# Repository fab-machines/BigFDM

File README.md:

<div align="center"><h1 style="font-family: courier;" align="center">BigFDM</h1></div>

<div align="center"></div>
<div align="center"><i>Open Source Large Scale 3D Printer</i></div>

Premises
--
We dream in a future of freedom, where open source hardware and [Fab Labs](https://fablabs.io/) enable people to fully understand how to make things they need, and where decentralized local production is customized to impact the surrounding community. Believing that empowering the user with knowledge about how to make machines, BigFDM wants to give to the world a powerful open source tool, to 3D print any large scale object you may need. And, together with [LaserDuo](http://laserduo.com/), this is one of the first steps in developing other machines sharing the same philosophy.

BigFDM
--
BigFDM is an open source large scale 3D printer. 

Taking advantage of what we have learned in [Fab Academy](https://fabacademy.org/), BigFDM has been developed using standard [Fab Lab equipment](https://docs.google.com/spreadsheets/d/1U-jcBWOJEjBT5A0N84IUubtcHKMEMtndQPLCkZCkVsU/pub?single=true&gid=0&output=html) and [techniques](http://fab.academany.org/2019/schedule.html). BigFDM was in fact built in [Fab Lab UAE](http://fablabuae.ae/) by Daniele Ingrassia with the help of Hashim Al Sakkaf. Reversing the consumer process, where knowledge and building of machines stays inside a black box managed by companies, BigFDM brings the advantages of an open source development:

- full awareness about how the machine works
- reproducible design
- possibility to customize the machine and/or to build new ones
- built as much as possible with local materials
- local self-fixing and self-production of the machine parts
- community can use and improve the design
- cheap alternative to large scale 3D printers
- use BigFDM as tool to produce other open source machines

BigFDM allows the printing of large scale objects, some examples can be orthotics and prosthesis, art installations, furniture, replacement parts, industrial design prototypes, molds for casting of full scale parts. Using  Fused Deposition Modeling (or FDM), it can use standard 2.85mm 3D printer filament, and as well common extruders nozzles.

**BigFDM specifications**:

- **800mm x 800mm x 900mm** printing area
- **dual extruder** with interchangeble nozzle
- **2.85mm** filament
- **0.4 - 1mm** nozzle size
- **NEMA 24/23**  stepper motors
- stages with **HiWin linear guides**
- anodized **aluminium frame**
- **heated bed** with 4 x 750W bed heaters
- **closed housing** of aluminum composite and acrylic
- fabbable **[satshakit](https://github.com/satshakit) and [satstep](https://github.com/satstep)** based electronics
- **integrated tablet** for machine control
- printing from **USB** drive
- BOM cost of about **2600€**
- power requirements 220V, 3000W max

Machine design
--

BigFDM has been designed considering to keep fixed from the beginning few constraints, which then influenced the rest of the subsequent design choices:

- the all machine parts must be inside a boxed main frame
- the machine XY stages design must be independent and consistent by itself
- the Z axis moves the bed up or down

These have been tought in order to bring the following benefits:

- a **compact design** that maximize the printing area while minizing the unused space (just 2mm between the bed supports and the housing!)
-  minimizing the unused space has **lowered the cost** of the frame and the housing parts
-  the main frame serves both as **structural squared reference** for all the machine parts and well as body for the housing
-  the **XY stages can be completely removed** without disassembling any other machine section
-  the **XY stage indipendent design** can be reused to develop other machines
-  the machine printing **area can be scaled up/down** just by changing the length of few machine parts

X and Y stages
--

The X and Y stages integrates all their components inside a squared plane frame of T-Slots profiles. Hiwin 15mm linear guides and 10mm GT2 belts, together with custom CNC milled POM parts have been used. Implementing a sort of **stages interoperability**, the stages frame can be completely detached from the machine, and virtually, plugged into a different machine having similar frame shape (eg a laser cutter). Similar interoperability has also been recursively kept for the Y axis, which can be modified/removed without changing the X axis. 

Z axis
--

The Z axis uses a single NEMA 24 to move 4 lead screws guided by 4 linear rods and bearings. A 4.7m closed loop HTD M3 belt is used to transmit the movement with a 2 to 1 pulley ratio. The lead screws are supported by ball bearing both at the top and the bottom, where also pulleys are attached. The corner structural parts are made with CNC milled 20mm acrylic, while the rods and bearing supports use CNC milled POM. Because of layer by layer downwards needed movements, the bed will never move fast, with the maximum speed used more for manual movements. The main frame is used as support structure for all the Z axis parts.

Bed
--

Made out of a 6mm aluminum plate cut with the CNC, the printing bed is suspended onto a lower frame structure by using 4 x 8mm DIN 912 bolts. The lower bed frame in turn is attached to the Z axis lead screws and linear rods. The lower frame is kept parallel to the upper stages by mechanically aligning it during the assembly, while the printing bed flatness can be finely tuned by screwing/unscrewing the 4 bolts. The design of the printing bed takes into account its **thermal expansion**, leaving a tolerance of expansion that exceeds the calculated one from the aluminum.

Housing
--

The housing has been developed to keep the internal temperature stable, and to allow the bed to quickly warmup. Because the machine parts have been constrained to be inside, the housing is attached directly to the main frame, and no additional parts are needed. The corners are made by 4mm aluminum composite (also called as dibond), while the windows are 6mm acryllic. Both materials have been CNC milled and the design is made in a way to fit two full sheets (about 2400x1250mm) of acrylic and one of aluminum composite. The tablet enclousure is made with the same materials, and allows to quickly remove it from the top.

Electronics
--
The electronics of BigFDM consists of a set of fabbable electronics, derived from the original **[satshakit](https://github.com/satshakit)** board and **[satstep](https://github.com/satstep)** stepper drivers, plus some additional boards. Following the used boards and their role in BigFDM.<br>

**[satshakit-mega](https://github.com/fab-machines/BigFDM/tree/master/electronics/satshakit-mega)**

Based on the [ATMega2560](https://www.microchip.com/wwwproducts/en/ATmega2560), this board provides the necessary microcontroller hardware for the Marlin manage its logic functionalities. Furthermore integrates an USB-to-Serial converter and USB port. Developed as general purpose board, not all the pins will be used. In the future this board will be a custom made solution for BigFDM. Link to the original [repo](https://github.com/satshakit/satshakit-mega).

---------

**[satstep6600](https://github.com/fab-machines/BigFDM/tree/master/electronics/satstep6600)**

Proved to have a robust design by being used in **[LaserDuo](http://laserduo.com/)** for more than a year, the satstep6600 is the stepper driver used to move the NEMA 23/24 used in BigFDM. Based on the Toshiba [TB6600HG](http://www.massmind.org/images/massmind/TB6600HG_datasheet.pdf) it can give up to 4.5A per coil to a single motor, whereas the NEMA 24 used will take a maximum of 4A. Link to the original [repo](https://github.com/satstep/satstep6600).

---------

**[Mosftet Board](https://github.com/fab-machines/BigFDM/tree/master/electronics/mosfet-board)**

Developed as an add-in to the satshakit-mega for BigFDM, the mosfet board integrates 4 mosfets to drive the nozzle heaters and the solid stae relay for the bed heaters, plus two slots for Pololu A4988 or similar stepper drivers. The A4988 are used to drive the two nozzle stepper motors.

---------

**[Sensor Board](https://github.com/fab-machines/BigFDM/tree/master/electronics/sensor-board)**

The sensor board integrates simple design with filtering capacitors and pull-up resistor. To this board the thermistors from the extruder and one of the thermistor of the bed heaters will be connected, together with the analog pins from the satshakit-mega.

---------

**[Endstop Board](https://github.com/fab-machines/BigFDM/tree/master/electronics/endstop-board)**

In a similar way of the Sensor Board, the Endstop Boards has some pull-up resistors and some capacitors to filter the noise coming from the endstops. To this board the endstops and the limits min (x-min, y-min, z-min) from the satshakit-mega will be connected. BigFDM uses normally open endstops. 

---------

Summary of the needed boards:

- 1 x satshakit-mega
- 3 x satstep6600
- 1 x mosfet board
- 1 x endstop board
- 1 x sensor board

To power all this electronics, and to switch on and off the heaters the following additonal parts are needed:

- 15A 24V power supply
- 25A 12V power supply
- 25A 230V solid state relay
- 3 x 24V fans (for the 3 x satstep6600)

Software
--
BigFDM uses **[Marlin firmware](https://github.com/MarlinFirmware/Marlin)** running on the satshakit-mega. The configuration changes have been applied into the configuration.h file, you can find it in the [config](https://github.com/fab-machines/BigFDM/tree/master/config) folder of this repository.

To control the machine and to stream the G-Code, [Repetier-Host](https://www.repetier.com/) has been used.

Build your own BigFDM
--

BigFDM is made by using a mix of fabricated and ready-made parts. The ready-made parts are selected to be as common/standard as possible, to make the sourcing of them easy in many countries. For both the raw materials needed for the fabricated parts, and the ready-made parts, refer to the Bill-of-Material for details: **[BigFDM BOM](https://github.com/fab-machines/BigFDM/raw/master/docs/BigFDM%20BOM.pdf)**

The fabrication of the parts mainly relays on standard [Fab Lab equipment](https://docs.google.com/spreadsheets/d/1U-jcBWOJEjBT5A0N84IUubtcHKMEMtndQPLCkZCkVsU/pub?single=true&gid=0&output=html). It will be therefore possible to make BigFDM in any of Fab Labs worldwide having it. Below a list of the required tools and machines:

- C02 laser cutter:
 - able to cut 8mm acrylic
 - needed for small acrylic parts
- large format wood CNC machine:
 - ShopBot or similar, size 2500x1250mm
 - to machine the aluminum parts (bed, Z axis supports)
 - to machine the aluminum composite for the housing
 - to machine the acrylic for the housing windows
 - to machine the POM parts (motor holders, attachments)
- 3D printer:
 - a small one (20x20x20cm) is sufficient
 - to print the filament/cables holders 
- Desktop format CNC machine:
 - Roland MDX50/MDX20/SRM20 or similar small machine (as well the cheap chinese ones)
 - to produce the required PCBs
- standard set of tools:
 - spanner key set
 - hex key set
 - DIN 875
 - calipers
 - rulers
 - screwdriver set
 - player set (grabber/cutter etc..)
 - clamps
 - rubber hummers

Both fabricated and ready-made parts have been modeled inside the **[BigFDM Fusion 360 model](https://github.com/fab-machines/BigFDM/raw/master/cad/BigFDM.f3d)**. Using Fusion is possible to export/prepare the parts for production in the following ways:

- right click save as STL, on a body that needs to be 3D printed
- use the built-in Fusion CAM processor for the machined parts
- project on a surface, and then right click export as DXF, for laser cutting
 
For more details about the tools and once you have all the fabricated and ready-made parts parts available, refer to the for step-by-step assembly instructions and tips: **[BigFDM Building Manual](https://github.com/fab-machines/BigFDM/wiki/Big-FDM-Building-Manual)** 

Big FDM requires different fabbable PCBs to work. Below the download links for the eagle files that you use to fabricate them:

- **[satshakit-mega schematic](https://raw.githubusercontent.com/fab-machines/BigFDM/master/electronics/satshakit-mega/satshakit-mega.sch)**, **[satshakit-mega board](https://raw.githubusercontent.com/fab-machines/BigFDM/master/electronics/satshakit-mega/satshakit-mega.brd)**
- **[satstep6600 schematic](https://github.com/fab-machines/BigFDM/raw/master/electronics/satstep6600/satstep6600.sch)**, **[satstep6600 board](https://github.com/fab-machines/BigFDM/raw/master/electronics/satstep6600/satstep6600.brd)**
- **[mosfet board schematic](https://github.com/fab-machines/BigFDM/raw/master/electronics/mosfet-board/mosfer-board.sch)**, **[mosfet board](https://github.com/fab-machines/BigFDM/raw/master/electronics/mosfet-board/mosfet-board.brd)**
- **[sensor board schematic](https://github.com/fab-machines/BigFDM/raw/master/electronics/sensor-board/sensor-board.sch)**, **[sensor board](https://github.com/fab-machines/BigFDM/raw/master/electronics/sensor-board/sensor-board.brd)**
- **[endstop board schematic](https://github.com/fab-machines/BigFDM/raw/master/electronics/endstop-board/endstop-board.sch)**, **[endstop board](https://github.com/fab-machines/BigFDM/raw/master/electronics/endstop-board/endstop-board.brd)**

Download here the configuration files (right click save as):

- **[Marlin BigFDM](https://github.com/fab-machines/BigFDM/raw/master/config/Marlin-1.1.x-BIGFDM.zip)** 
- **[Cura profile settings for 1mm nozzle](https://github.com/fab-machines/BigFDM/raw/master/config/Cura_BigFDM.curaprofile)** 
- **[Cura  machine settings](https://github.com/fab-machines/BigFDM/raw/master/config/BigFDM_machine_settings.png)**
- **[Cura extruder settings](https://github.com/fab-machines/BigFDM/raw/master/config/BigFDM_extruder_settings.png)**

Known issues
--

- the extruder used is a dual Geetech MK8, which is good up to 0.5mm nozzle but has difficulties in keeping the temperature with an 1mm nozzle; in the future will be replaced by a custom made extruder supporting nozzles up to 2mm

- because of the difficulties for the extruder to warmup, to save time it is recommended to start heating it manually whenever possible before starting printing 

- the electronics setup requires improvements, especially a custom made board in place of the satshakit-mega and an additonal all-in-one board, replacing the mosfet, sensor and endstop boards

- the Z axis design needs multiple parts for the supporting corners of the lead screws and the linear rods; in the future replaced by an unique block of CNC milled aluminum

- the G-Code streaming from the tablet is sometimes gets corrupted and/or interrupts suddenly; is needed to use an higher quality shielded USB cable, or  to try Octoprint instead of Repetier host as G-Code streamer

Media
--
**BigFDM printing**

**How to Make BigFDM: Tunisia Workshop at [Fab Lab ENIT](https://www.facebook.com/FabLabENIT/)**

**BigFDM pictures**

<br><br><br>

<br><br><br>

<br><br><br>

Author
--

The author of BigFDM is:

- **Daniele Ingrassia, daniele@inmachines.net**
- **[InMachines Ingrassia GmbH](https://www.inmachines.net/)**

**Project Helper:**<br>
- **[Hashim Al Sakkaf](http://archive.fabacademy.org/fabacademy2017/fablabuae/students/154/)**

Donations
--

Our dream is to have impact by making **open source machines digitally available and locally produced anywhere in world**. We plan to open a dedicated Fab Lab to foster open machine building and digital fabrication research. Practically several tasks and many expensens have to be sustained to give this dream the chance to have a future. Such as the renting of a proper space, the making/purchasing of proper equipment, the sustainability of our work and lifes. If you share this mindset and BigFDM is useful to you, please help us to make this dream a reality by donating your support:

Acknowledgements
--

The development of this machine has been funded by:<br>
**[German Federal Ministry of Education and Research](https://www.bmbf.de/en/index.html)**

Funds implemented by:<br>
**[OpenLab Hamburg](http://openlab-hamburg.de/startpage/)**<br>
[Helmut-Schmidt-Universität Universität der Bundeswehr](https://www.hsu-hh.de/en/)<br>
Laboratorium Fertigungstechnik<br>
Holstenhofweg 85<br>
22043 Hamburg<br>

Thanks:<br>
<br>
**[Fablab UAE](http://fablabuae.ae/)**<br />
176 6 D St - Satwa <br />
Dubai - United Arab Emirates<br />
fablabuae@gmail.com

**Paul Anand**

License
-- 
The BigFDM, its hardware design, CAD, BOM, settings and relative files are are released under the following open source license:

- CERN Open Hardware Licence Version 2 Weakly Reciprocal - **[CERN-OHL-W](LICENSE_CERN_OHL_W_V2.txt)**

Note
--

This documentation will be continuously improved as soon there are updates and/or improvements on the machine.

Disclaimer  
--

<div class="align-justify">
This hardware/software is provided "as is", and you use the hardware/software at your own risk. Under no circumstances shall any author be liable for direct, indirect, special, incidental, or consequential damages resulting from the use, misuse, or inability to use this hardware/software, even if the authors have been advised of the possibility of such damages.</div>

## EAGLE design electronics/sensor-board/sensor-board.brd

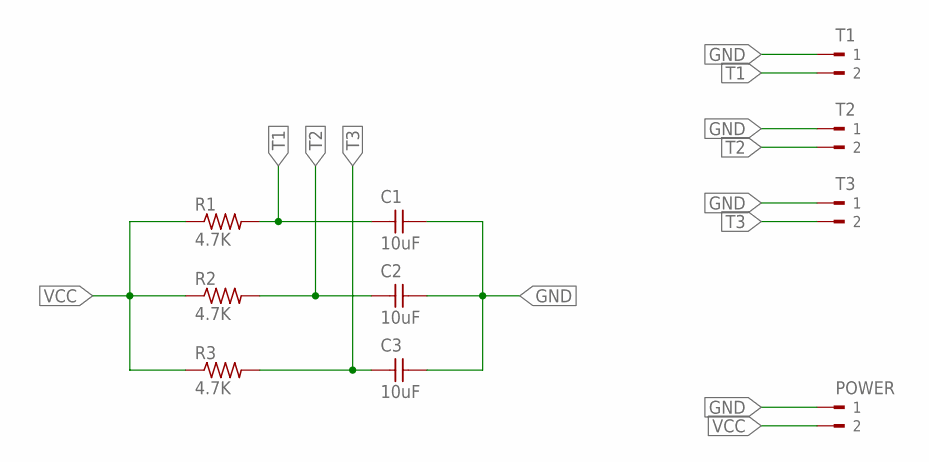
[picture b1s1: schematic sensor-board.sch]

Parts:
C1, C2, C3: 10uF; 1206
POWER: PM5.08/2/90BLK; WEIDMULLER_PM5.08_2
R1, R2, R3: 4.7K; R1206FAB
T1, T2, T3: PM5.08/2/90BLK; WEIDMULLER_PM5.08_2

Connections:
GND: C1.2, C2.2, C3.2, POWER.1, T1.1, T2.1, T3.1
T1: C1.1, R1.2, T1.2
T2: C2.1, R2.2, T2.2
T3: C3.1, R3.2, T3.2
VCC: POWER.2, R1.1, R2.1, R3.1

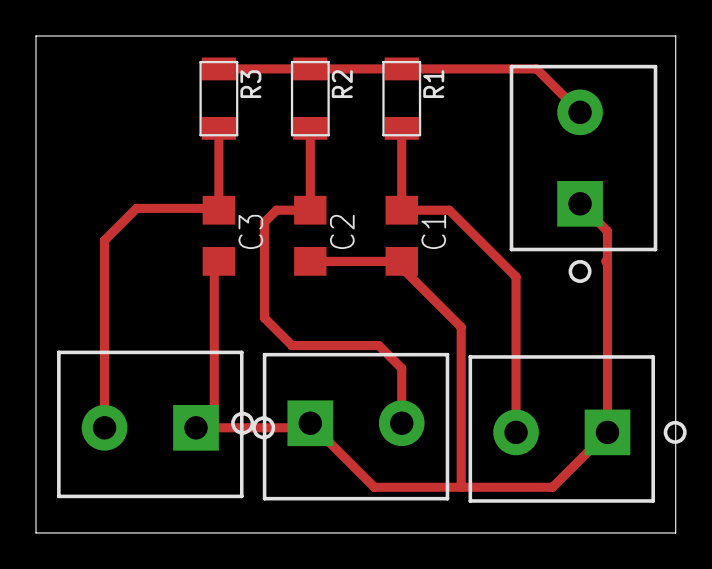
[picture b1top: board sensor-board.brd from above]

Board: 2 copper layers, 35.5 x 27.6 mm, 10 parts (0 on the bottom side), 5 nets.

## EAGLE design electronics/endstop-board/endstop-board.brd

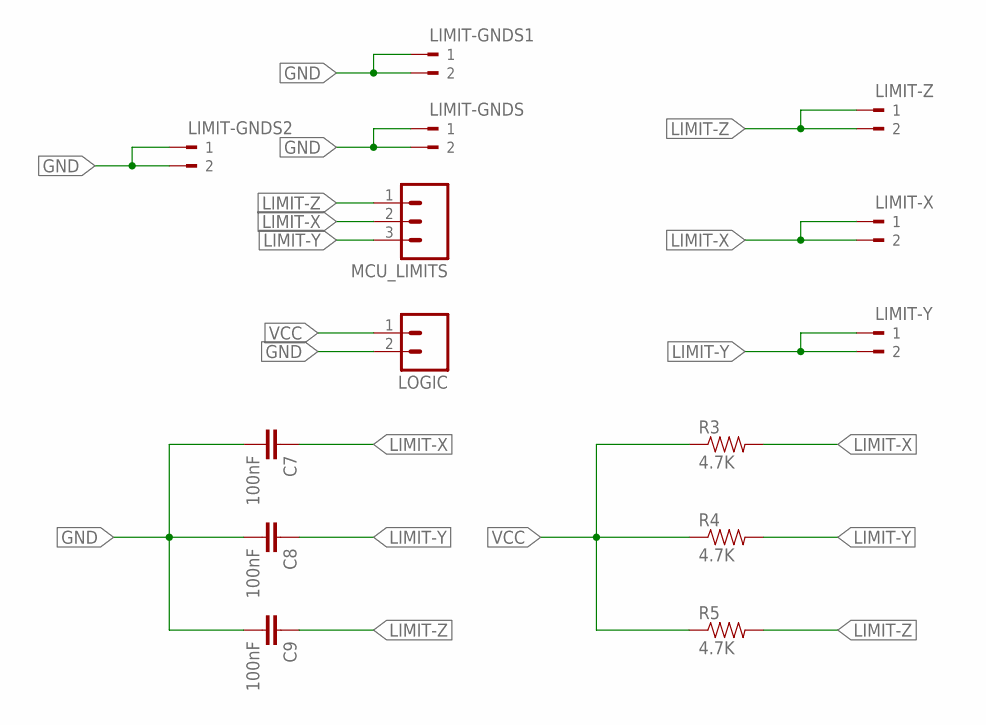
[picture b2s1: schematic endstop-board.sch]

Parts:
C7, C8, C9: 100nF; 1206
LIMIT-GNDS, LIMIT-GNDS1, LIMIT-GNDS2: PM5.08/2/90BLK; WEIDMULLER_PM5.08_2
LIMIT-X: PM5.08/2/90BLK; WEIDMULLER_PM5.08_2
LIMIT-Y: PM5.08/2/90BLK; WEIDMULLER_PM5.08_2
LIMIT-Z: PM5.08/2/90BLK; WEIDMULLER_PM5.08_2
LOGIC: M02; 02P
MCU_LIMITS: M03; 03P
R3, R4, R5: 4.7K; 1206

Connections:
GND: C7.2, C8.2, C9.2, LIMIT-GNDS.1, LIMIT-GNDS.2, LIMIT-GNDS1.1, LIMIT-GNDS1.2, LIMIT-GNDS2.1, LIMIT-GNDS2.2, LOGIC.2
LIMIT-X: C7.1, LIMIT-X.1, LIMIT-X.2, MCU_LIMITS.2, R3.2
LIMIT-Y: C8.1, LIMIT-Y.1, LIMIT-Y.2, MCU_LIMITS.3, R4.2
LIMIT-Z: C9.1, LIMIT-Z.1, LIMIT-Z.2, MCU_LIMITS.1, R5.2
VCC: LOGIC.1, R3.1, R4.1, R5.1

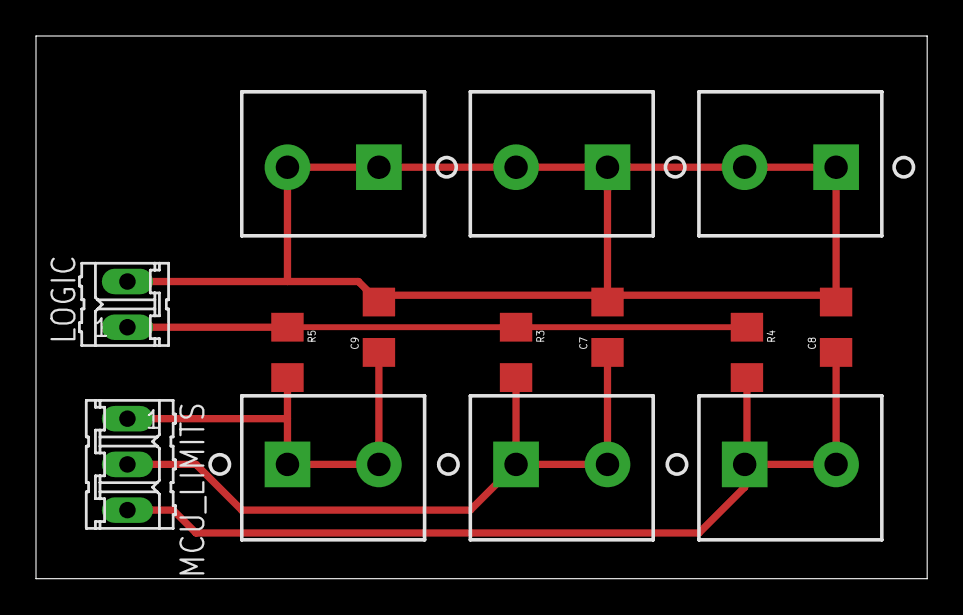
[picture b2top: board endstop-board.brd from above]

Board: 2 copper layers, 49.5 x 30.1 mm, 14 parts (0 on the bottom side), 5 nets.

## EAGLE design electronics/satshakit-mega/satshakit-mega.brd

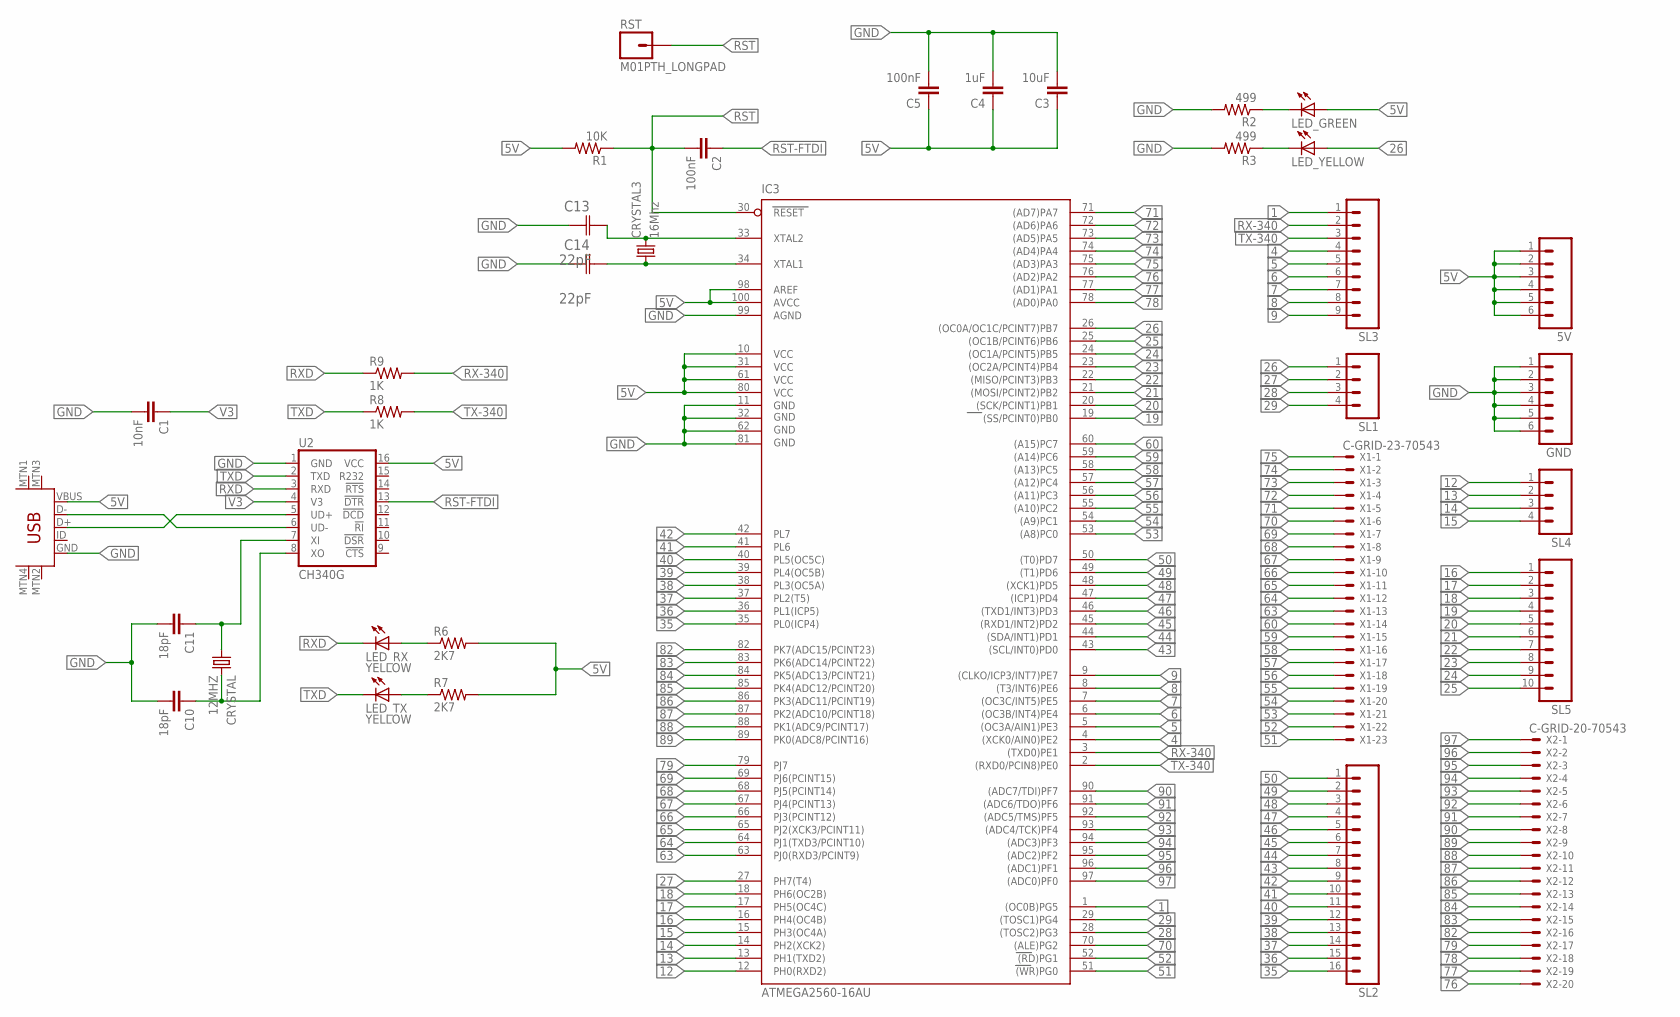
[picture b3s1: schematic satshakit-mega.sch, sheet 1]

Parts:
5V: M06; 06P
C1: 10nF; 1206
C2, C5: 100nF; 1206
C3: 10uF; 1206
C4: 1uF; 1206
C10, C11: 18pF; 1206
C13, C14: 22pF; CAPC3216X178N
CRYSTAL: 12MHZ; CSM-7X-DU
CRYSTAL3: 16Mhz; CSM-7X-DU
GND: M06; 06P
IC3: ATMEGA2560-16AU; TQFP100
LED_GREEN: LED1206; 1206
LED_RX: YELLOW; LED1206
LED_TX: YELLOW; LED1206
LED_YELLOW: LED1206; 1206
R1: 10K; R1206
R2, R3: 499; 1206
R6, R7: 2K7; R1206
R8, R9: 1K; R1206
RST: M01PTH_LONGPAD; 1X01_LONGPAD
SL1, SL4: M04; 04P
SL2: M16; 16P
SL3: M09; 09P
SL5: M10; 10P
U2: CH340G; SO016
U$7: USB-MINIB-5PIN; USB-MINIB
X1: C-GRID-23-70543; 70543-23
X2: C-GRID-20-70543; 70543-20

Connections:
1: IC3.1 ((OC0B)PG5), SL3.1
4: IC3.4 ((XCK0/AIN0)PE2), SL3.4
5: IC3.5 ((OC3A/AIN1)PE3), SL3.5
5V: 5V.1, 5V.2, 5V.3, 5V.4, 5V.5, 5V.6, C3.1, C4.1, C5.1, IC3.10 (VCC), IC3.31 (VCC1), IC3.61 (VCC2), IC3.80 (VCC3), IC3.98 (AREF), IC3.100 (AVCC), LED_GREEN.1 (A), R1.2, R6.2, R7.2, U2.16 (VCC), U$7.VBUS
6: IC3.6 ((OC3B/INT4)PE4), SL3.6
7: IC3.7 ((OC3C/INT5)PE5), SL3.7
8: IC3.8 ((T3/INT6)PE6), SL3.8
9: IC3.9 ((CLKO/ICP3/INT7)PE7), SL3.9
12: IC3.12 (PH0(RXD2)), SL4.1
13: IC3.13 (PH1(TXD2)), SL4.2
14: IC3.14 (PH2(XCK2)), SL4.3
15: IC3.15 (PH3(OC4A)), SL4.4
16: IC3.16 (PH4(OC4B)), SL5.1
17: IC3.17 (PH5(OC4C)), SL5.2
18: IC3.18 (PH6(OC2B)), SL5.3
19: IC3.19 ((SS/PCINT0)PB0), SL5.4
20: IC3.20 ((SCK/PCINT1)PB1), SL5.5
21: IC3.21 ((MOSI/PCINT2)PB2), SL5.6
22: IC3.22 ((MISO/PCINT3)PB3), SL5.7
23: IC3.23 ((OC2A/PCINT4)PB4), SL5.8
24: IC3.24 ((OC1A/PCINT5)PB5), SL5.9
25: IC3.25 ((OC1B/PCINT6)PB6), SL5.10
26: IC3.26 ((OC0A/OC1C/PCINT7)PB7), LED_YELLOW.1 (A), SL1.1
27: IC3.27 (PH7(T4)), SL1.2
28: IC3.28 ((TOSC2)PG3), SL1.3
29: IC3.29 ((TOSC1)PG4), SL1.4
35: IC3.35 (PL0(ICP4)), SL2.16
36: IC3.36 (PL1(ICP5)), SL2.15
37: IC3.37 (PL2(T5)), SL2.14
38: IC3.38 (PL3(OC5A)), SL2.13
39: IC3.39 (PL4(OC5B)), SL2.12
40: IC3.40 (PL5(OC5C)), SL2.11
41: IC3.41 (PL6), SL2.10
42: IC3.42 (PL7), SL2.9
43: IC3.43 ((SCL/INT0)PD0), SL2.8
44: IC3.44 ((SDA/INT1)PD1), SL2.7
45: IC3.45 ((RXD1/INT2)PD2), SL2.6
46: IC3.46 ((TXD1/INT3)PD3), SL2.5
47: IC3.47 ((ICP1)PD4), SL2.4
48: IC3.48 ((XCK1)PD5), SL2.3
49: IC3.49 ((T1)PD6), SL2.2
50: IC3.50 ((T0)PD7), SL2.1
51: IC3.51 ((WR)PG0), X1.23
52: IC3.52 ((RD)PG1), X1.22
53: IC3.53 ((A8)PC0), X1.21
54: IC3.54 ((A9)PC1), X1.20
55: IC3.55 ((A10)PC2), X1.19
56: IC3.56 ((A11)PC3), X1.18
57: IC3.57 ((A12)PC4), X1.17
58: IC3.58 ((A13)PC5), X1.16
59: IC3.59 ((A14)PC6), X1.15
60: IC3.60 ((A15)PC7), X1.14
63: IC3.63 (PJ0(RXD3/PCINT9)), X1.13
64: IC3.64 (PJ1(TXD3/PCINT10)), X1.12
65: IC3.65 (PJ2(XCK3/PCINT11)), X1.11
66: IC3.66 (PJ3(PCINT12)), X1.10
67: IC3.67 (PJ4(PCINT13)), X1.9
68: IC3.68 (PJ5(PCINT14)), X1.8
69: IC3.69 (PJ6(PCINT15)), X1.7
70: IC3.70 ((ALE)PG2), X1.6
71: IC3.71 ((AD7)PA7), X1.5
72: IC3.72 ((AD6)PA6), X1.4
73: IC3.73 ((AD5)PA5), X1.3
74: IC3.74 ((AD4)PA4), X1.2
75: IC3.75 ((AD3)PA3), X1.1
76: IC3.76 ((AD2)PA2), X2.20
77: IC3.77 ((AD1)PA1), X2.19
78: IC3.78 ((AD0)PA0), X2.18
79: IC3.79 (PJ7), X2.17
82: IC3.82 (PK7(ADC15/PCINT23)), X2.16
83: IC3.83 (PK6(ADC14/PCINT22)), X2.15
84: IC3.84 (PK5(ADC13/PCINT21)), X2.14
85: IC3.85 (PK4(ADC12/PCINT20)), X2.13
86: IC3.86 (PK3(ADC11/PCINT19)), X2.12
87: IC3.87 (PK2(ADC10/PCINT18)), X2.11
88: IC3.88 (PK1(ADC9/PCINT17)), X2.10
89: IC3.89 (PK0(ADC8/PCINT16)), X2.9
90: IC3.90 ((ADC7/TDI)PF7), X2.8
91: IC3.91 ((ADC6/TDO)PF6), X2.7
92: IC3.92 ((ADC5/TMS)PF5), X2.6
93: IC3.93 ((ADC4/TCK)PF4), X2.5
94: IC3.94 ((ADC3)PF3), X2.4
95: IC3.95 ((ADC2)PF2), X2.3
96: IC3.96 ((ADC1)PF1), X2.2
97: IC3.97 ((ADC0)PF0), X2.1
GND: C1.2, C3.2, C4.2, C5.2, C10.2, C11.2, C13.1 (C1), C14.1 (C1), GND.1, GND.2, GND.3, GND.4, GND.5, GND.6, IC3.11 (GND), IC3.32 (GND1), IC3.62 (GND2), IC3.81 (GND3), IC3.99 (AGND), R2.2, R3.2, U2.1 (GND), U$7.GND
unnamed: U2.5 (UD+), U$7.D+
unnamed: LED_RX.1 (A), R6.1
unnamed: U2.6 (UD-), U$7.D-
unnamed: C14.2 (C2), CRYSTAL3.1, IC3.34 (XTAL1)
unnamed: C13.2 (C2), CRYSTAL3.2, IC3.33 (XTAL2)
unnamed: LED_YELLOW.2 (C), R3.1
unnamed: LED_TX.1 (A), R7.1
unnamed: LED_GREEN.2 (C), R2.1
OSC_IN: C10.1, CRYSTAL.2, U2.8 (XO)
OSC_OUT: C11.1, CRYSTAL.1, U2.7 (XI)
RST: C2.2, IC3.30 (RESET), R1.1, RST.1
RST-FTDI: C2.1, U2.13 (!DTR)
RX-340: IC3.3 ((TXD0)PE1), R9.2, SL3.2
RXD: LED_RX.2 (C), R9.1, U2.3 (RXD)
TX-340: IC3.2 ((RXD0/PCIN8)PE0), R8.2, SL3.3
TXD: LED_TX.2 (C), R8.1, U2.2 (TXD)
V3: C1.1, U2.4 (V3)

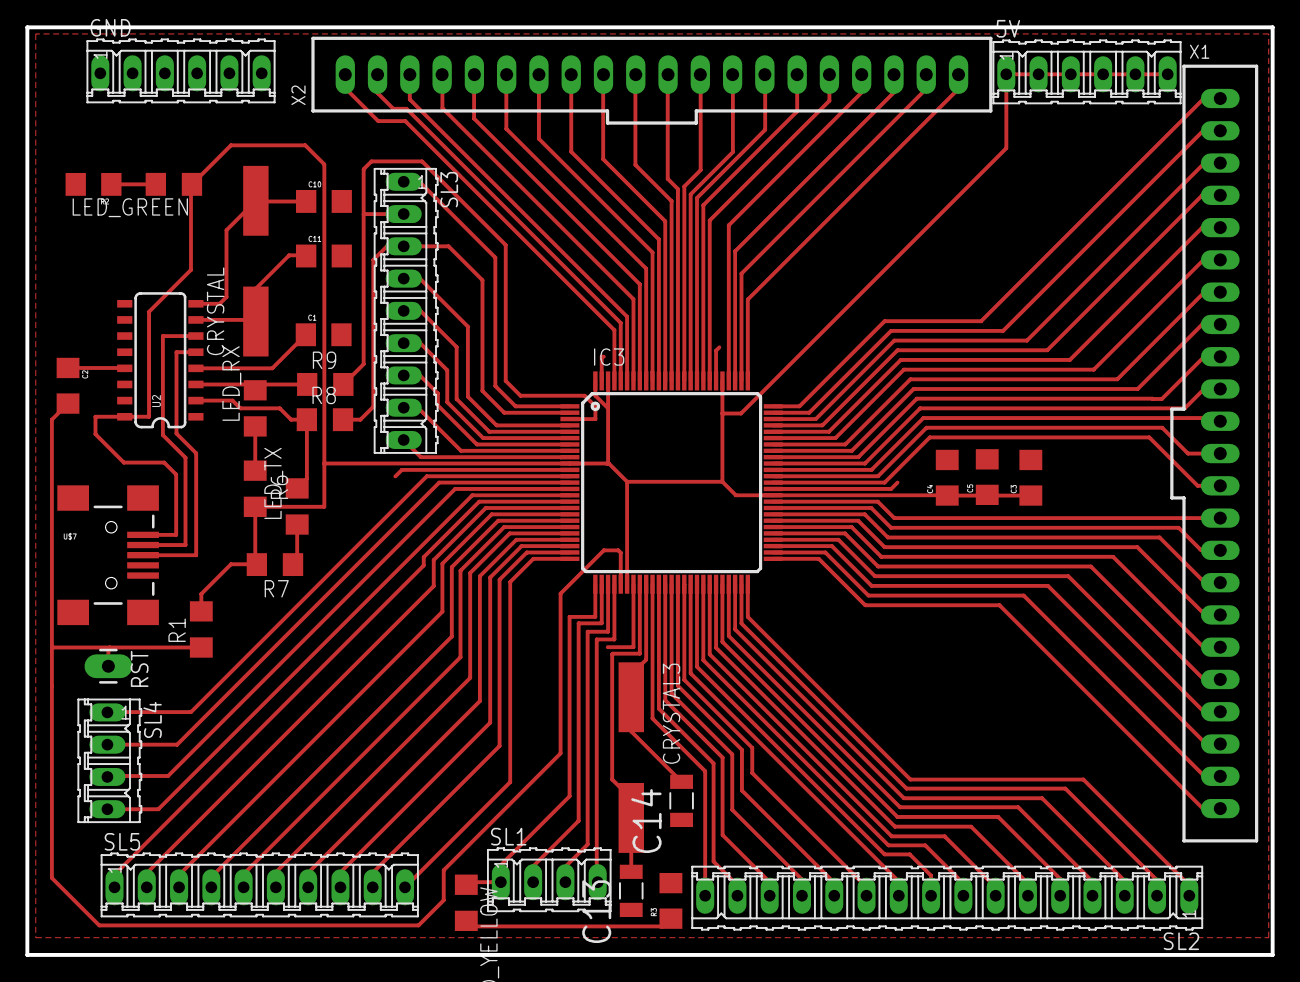
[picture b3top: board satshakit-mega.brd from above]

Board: 2 copper layers, 98.0 x 73.0 mm, 35 parts (0 on the bottom side), 103 nets.

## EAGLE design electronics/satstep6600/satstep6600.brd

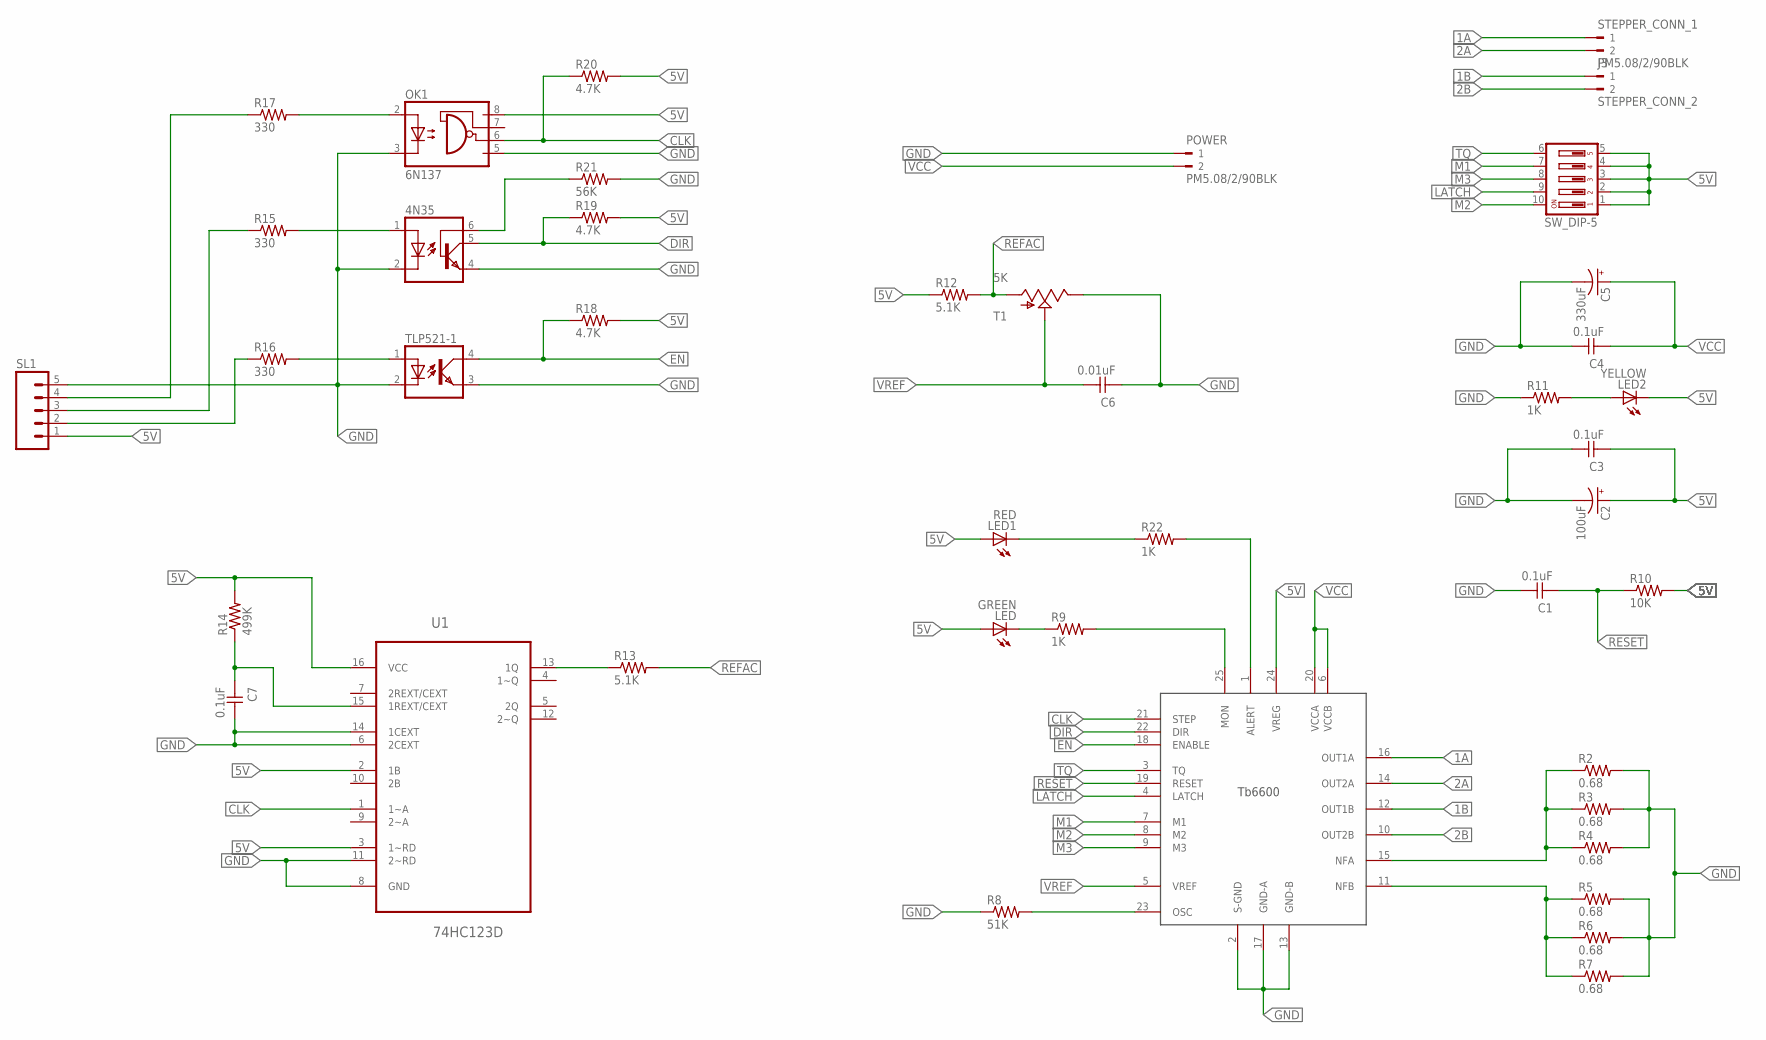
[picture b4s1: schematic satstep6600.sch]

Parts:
4N35: 4N35; DIL06
C1, C3, C4, C7: 0.1uF; 1206
C2: 100uF; PANASONIC_C
C5: 330uF; CPOL-RADIAL-1000UF-63V
C6: 0.01uF; 1206
J3: STEPPER_CONN_2; WEIDMULLER_PM5.08_2
LED: GREEN; 1206
LED1: RED; 1206
LED2: YELLOW; 1206
OK1: 6N137; DIL08
POWER: PM5.08/2/90BLK; WEIDMULLER_PM5.08_2
R2, R3, R4, R5, R6, R7: 0.68; 2512
R8: 51K; R1206
R9, R11, R22: 1K; R1206
R10: 10K; R1206
R12, R13: 5.1K; R1206
R14: 499K; R1206
R15, R16, R17: 330; R1206
R18, R19, R20: 4.7K; R1206
R21: 56K; R1206
SL1: M05; 05P
STEPPER_CONN_1: PM5.08/2/90BLK; WEIDMULLER_PM5.08_2
SW_DIP-5: SD4-05
T1: 5K; TS53YL104MR10_TRIMMER
TLP521-1: PC817; DIL04
U1: 74HC123D; SOIC127P600X175-16N
U$1: TB6600HG; P-HZIP25-1.00G

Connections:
1A: STEPPER_CONN_1.1, U$1.16 (OUT1A)
1B: J3.1, U$1.12 (OUT1B)
2A: STEPPER_CONN_1.2, U$1.14 (OUT2A)
2B: J3.2, U$1.10 (OUT2B)
5V: C2.+, C3.1, LED.1 (A), LED1.1 (A), LED2.2 (C), OK1.8 (VCC), R10.2, R12.1, R14.2, R18.2, R19.2, R20.2, SL1.1, SW_DIP-5.1, SW_DIP-5.2, SW_DIP-5.3, SW_DIP-5.4, SW_DIP-5.5, U1.2 (1B), U1.3 (1~RD), U1.16 (VCC), U$1.24 (VREG)
ALERT: R22.2, U$1.1 (ALERT)
CLK: OK1.6 (VO), R20.1, U1.1 (1~A), U$1.21 (STEP)
DIR: 4N35.5 (COL), R19.1, U$1.22 (DIR)
EN: R18.1, TLP521-1.4 (COL), U$1.18 (ENABLE)
GND: 4N35.2 (C), 4N35.4 (EMI), C1.2, C2.-, C3.2, C4.2, C5.2 (-), C6.1, C7.2, OK1.3 (C), OK1.5 (GND), POWER.1, R2.2, R3.2, R4.2, R5.2, R6.2, R7.2, R8.1, R11.1, R21.2, SL1.5, T1.P$2 (E), TLP521-1.2 (C), TLP521-1.3 (EMIT), U1.6 (2CEXT), U1.8 (GND), U1.11 (2~RD), U1.14 (1CEXT), U$1.2 (S-GND), U$1.13 (GND-B), U$1.17 (GND-A)
LATCH: SW_DIP-5.9, U$1.4 (LATCH)
M1: SW_DIP-5.7, U$1.7 (M1)
M2: SW_DIP-5.10, U$1.8 (M2)
M3: SW_DIP-5.8, U$1.9 (M3)
unnamed: R5.1, R6.1, R7.1, U$1.11 (NFB)
unnamed: R8.2, U$1.23 (OSC)
unnamed: LED.2 (C), R9.1
unnamed: R2.1, R3.1, R4.1, U$1.15 (NFA)
unnamed: LED1.2 (C), R22.1
unnamed: LED2.1 (A), R11.2
unnamed: R13.1, U1.13 (1Q)
unnamed: C7.1, R14.1, U1.15 (1REXT/CEXT)
unnamed: R16.2, TLP521-1.1 (A)
unnamed: 4N35.1 (A), R15.2
unnamed: OK1.2 (A), R17.2
unnamed: 4N35.6 (BAS), R21.1
unnamed: R16.1, SL1.2
unnamed: R15.1, SL1.3
unnamed: R17.1, SL1.4
unnamed: R9.2, U$1.25 (MON)
REFAC: R12.2, R13.2, T1.P$3 (A)
RESET: C1.1, R10.1, U$1.19 (RESET)
TQ: SW_DIP-5.6, U$1.3 (TQ)
VCC: C4.1, C5.1 (+), POWER.2, U$1.6 (VCCB), U$1.20 (VCCA)
VREF: C6.2, T1.P$1 (S), U$1.5 (VREF)

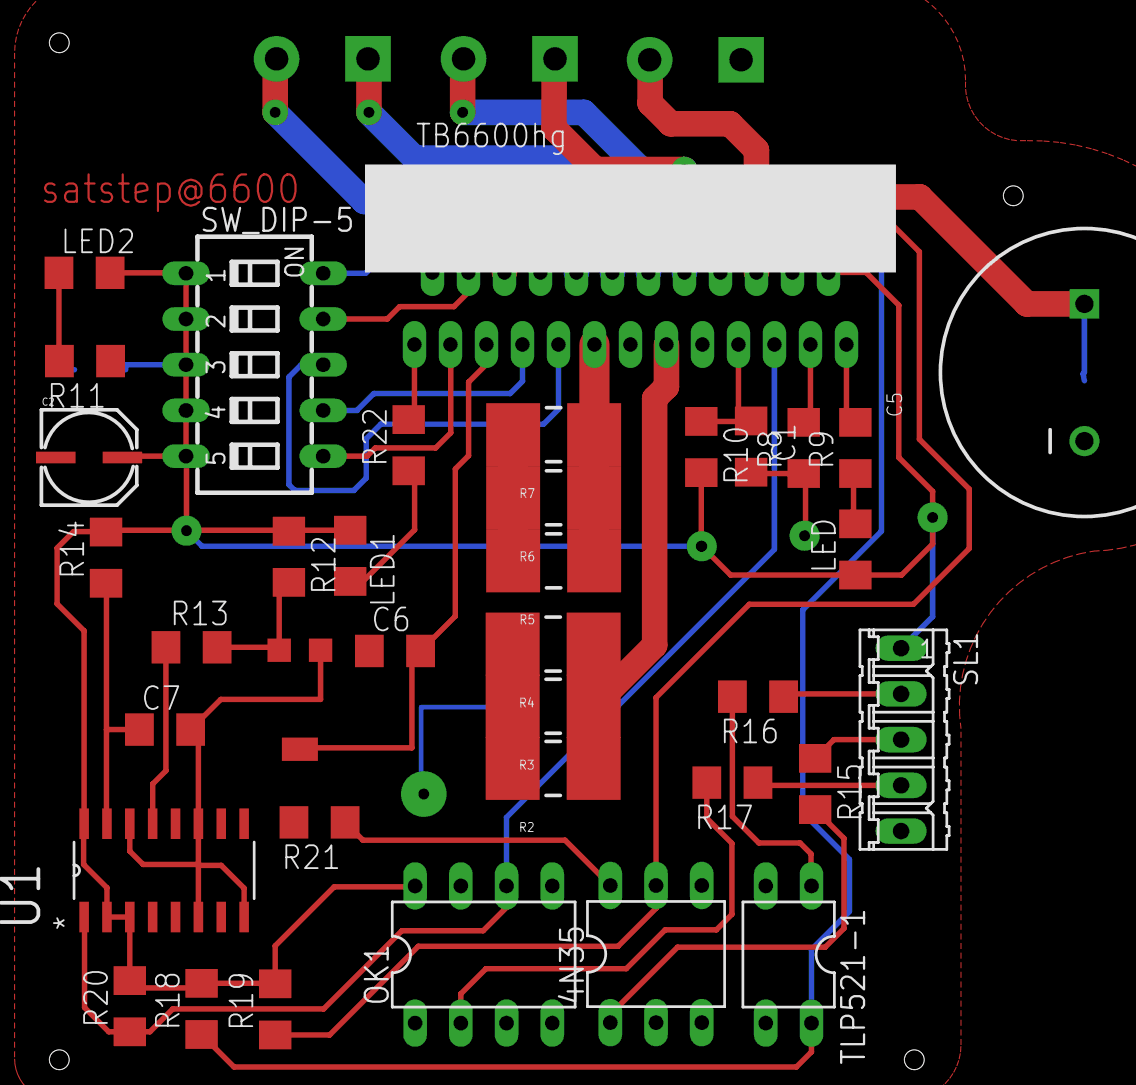
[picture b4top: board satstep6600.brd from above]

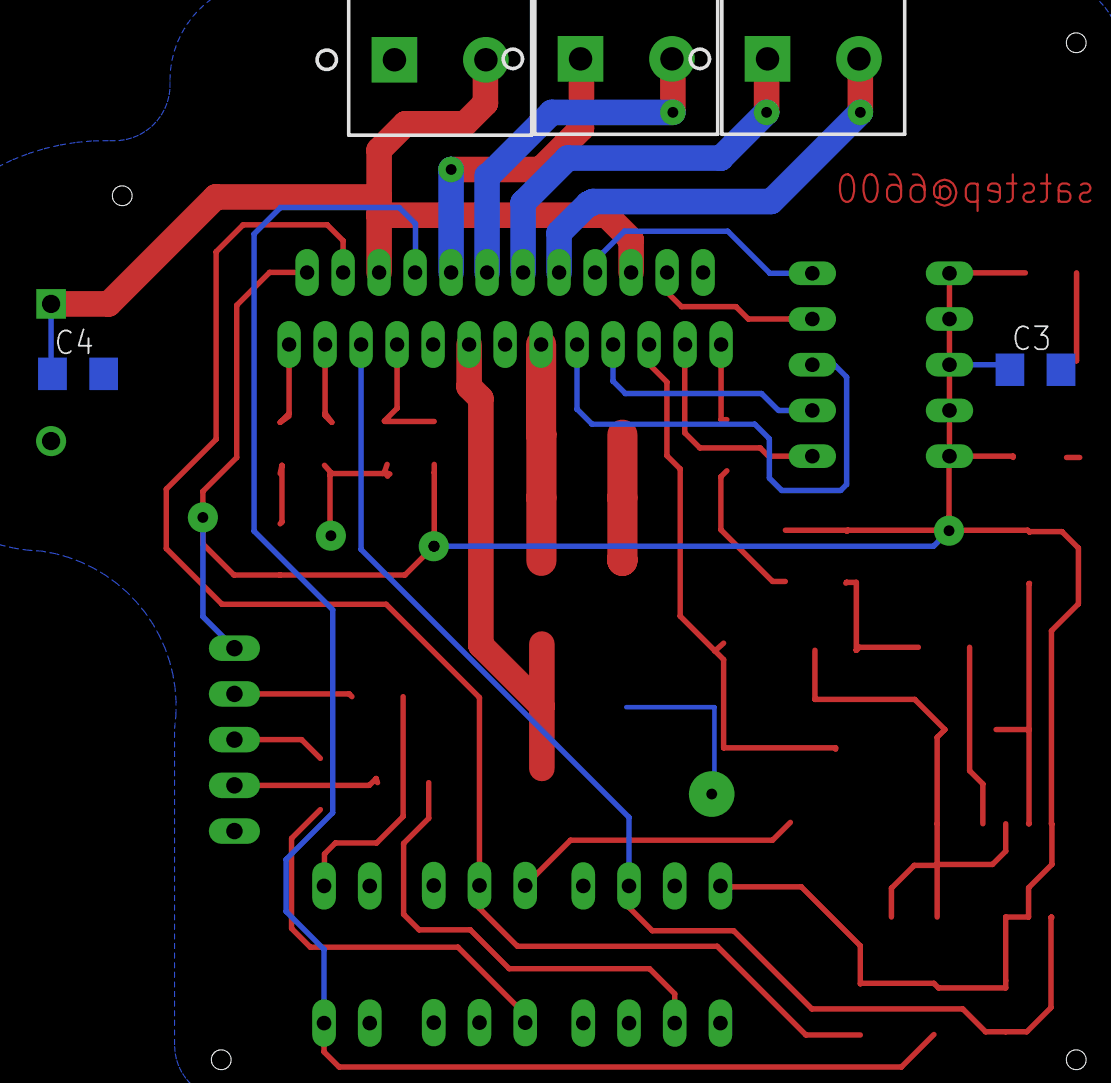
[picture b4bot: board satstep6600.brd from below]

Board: 2 copper layers, 42 parts (5 on the bottom side), 35 nets.

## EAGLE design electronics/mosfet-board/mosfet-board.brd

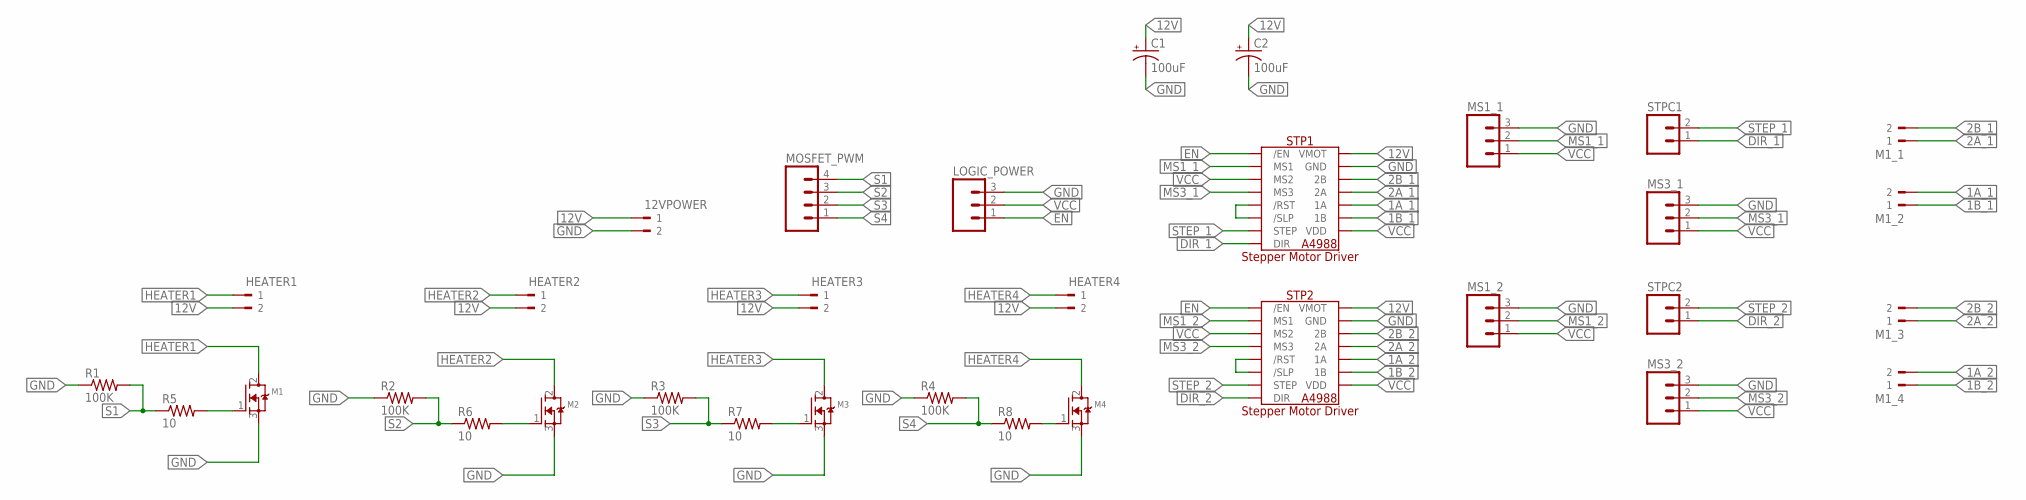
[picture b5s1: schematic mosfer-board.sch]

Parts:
12VPOWER: PM5.08/2/90BLK; WEIDMULLER_PM5.08_2
C1, C2: 100uF; CPOL-RADIAL-2.5MM-6.5MM
HEATER1, HEATER2, HEATER3, HEATER4: PM5.08/2/90BLK; WEIDMULLER_PM5.08_2
LOGIC_POWER: M03; 03P
M1, M2, M3, M4: MOSFET-NGDS_TO220V; TO220V
M1_1, M1_2, M1_3, M1_4: PM5.08/2/90BLK; WEIDMULLER_PM5.08_2
MOSFET_PWM: M04; 04P
MS1_1, MS1_2, MS3_1, MS3_2: M03; 03P
R1, R2, R3, R4: 100K; R1206FAB
R5, R6, R7, R8: 10; R1206FAB
STP1, STP2: A4988_STEP
STPC1, STPC2: M02; 02P

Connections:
1A_1: M1_2.2, STP1.1A
1A_2: M1_4.2, STP2.1A
1B_1: M1_2.1, STP1.1B
1B_2: M1_4.1, STP2.1B
2A_1: M1_1.1, STP1.2A
2A_2: M1_3.1, STP2.2A
2B_1: M1_1.2, STP1.2B
2B_2: M1_3.2, STP2.2B
12V: 12VPOWER.1, C1.1 (+), C2.1 (+), HEATER1.2, HEATER2.2, HEATER3.2, HEATER4.2, STP1.VMOT, STP2.VMOT
DIR_1: STP1.DIR, STPC1.1
DIR_2: STP2.DIR, STPC2.1
EN: LOGIC_POWER.1, STP1./EN, STP2./EN
GND: 12VPOWER.2, C1.2 (-), C2.2 (-), LOGIC_POWER.3, M1.3 (S), M2.3 (S), M3.3 (S), M4.3 (S), MS1_1.3, MS1_2.3, MS3_1.3, MS3_2.3, R1.1, R2.1, R3.1, R4.1, STP1.GND, STP1.GND2 (GND), STP2.GND, STP2.GND2 (GND)
HEATER1: HEATER1.1, M1.2 (D)
HEATER2: HEATER2.1, M2.2 (D)
HEATER3: HEATER3.1, M3.2 (D)
HEATER4: HEATER4.1, M4.2 (D)
MS1_1: MS1_1.2, STP1.MS1
MS1_2: MS1_2.2, STP2.MS1
MS3_1: MS3_1.2, STP1.MS3
MS3_2: MS3_2.2, STP2.MS3
unnamed: STP1./RST, STP1./SLP
unnamed: STP2./RST, STP2./SLP
unnamed: M3.1 (G), R7.2
unnamed: M2.1 (G), R6.2
unnamed: M1.1 (G), R5.2
unnamed: M4.1 (G), R8.2
S1: MOSFET_PWM.4, R1.2, R5.1
S2: MOSFET_PWM.3, R2.2, R6.1
S3: MOSFET_PWM.2, R3.2, R7.1
S4: MOSFET_PWM.1, R4.2, R8.1
STEP_1: STP1.STEP, STPC1.2
STEP_2: STP2.STEP, STPC2.2
VCC: LOGIC_POWER.2, MS1_1.1, MS1_2.1, MS3_1.1, MS3_2.1, STP1.MS2, STP1.VDD, STP2.MS2, STP2.VDD

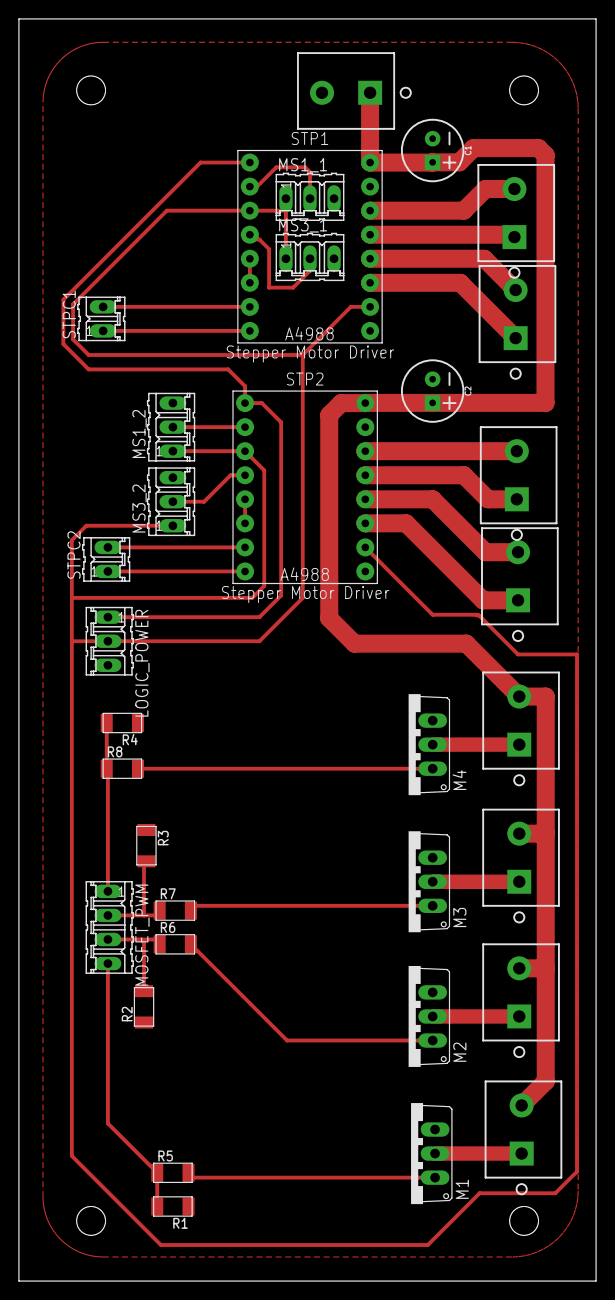
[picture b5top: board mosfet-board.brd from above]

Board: 2 copper layers, 60.9 x 133.3 mm, 33 parts (0 on the bottom side), 34 nets.

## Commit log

2019-06-20 updated manual
2019-06-21 added manual pics
2019-06-23 ENIT is the best Fab Lab in the World
2019-06-28 added config files
2019-07-01 added Acknowledgements
2019-07-01 added Fab Academy links
2019-07-01 added more info into the README
2019-07-05 updated bom, cad file, README
2019-07-05 removed html bom
2019-07-05 added renderings
2019-07-05 fixed readme
2019-07-05 updated renderings
2019-07-06 added housing description
2019-07-06 added explode
2019-07-06 added y rendering
2019-07-06 updated README, added media
2019-07-06 fixed links
2019-07-06 added technical pic
2019-07-06 added link
2019-07-06 added real assembly pics
2019-07-06 updated specs
2019-07-06 updated BOM
2019-07-08 updated open source design
2021-11-04 Update README.md
    Updated author and license sections.

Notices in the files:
parts and their libraries:
01_SparkFun: Licensing: CC v3.0 Share-Alike You are welcome to use this library for commercial purposes.
SparkFun-Capacitors: Licensing: Creative Commons ShareAlike 4.0 International - https://creativecommons.org/licenses/by-sa/4.0
